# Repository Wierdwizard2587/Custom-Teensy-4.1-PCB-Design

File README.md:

# Custom Teensy 4.1 Microcontroller PCB

## Overview

This repository covers the design of my custom take on the Teensy 4.1 from PJRC. [Teensy 4.1 Site](https://www.pjrc.com/store/teensy41.html). I took inspiration from [jenschrs design](https://github.com/jenschr/Teensy-4.1-example) who incorporated usb-c rather than the intended USB-Micro, but lacked the SD slot, expandable RAM and flash memory, and PHY Ethernet IC and RJ45 Connection Like the original. 

This Design, following the Teensy 4.1 official Schematic Features a 6 layer design with dedicated GND and 3.3V plane’s, and possesses the same RAM, Flash, Boot loader and MCU components as the original Teensy 4.1, but the 3.3V regulator was swapped for a NCP692 regulator providing essentially the same specs. 

The Following are notable features in the Boards design:

- 2x USB-C connections, one for serial programming and power, and the other a host port for communication with serial to other devices
- Expandable IC footprints for a combination of either 2x additional 16mb PSRAM or 1x 16mb PSRAM and 1x 64mb FLASH
- DP83825L Ethernet PHY IC for interfacing with the MCU and the RJ45 Ethernet connector attached to the board for 10/100mbps internet
- micro SD slot

After assembling the first prototype with the supplied stencil from JLCPCB and a hot plate, and resolving a short issue from a solder bridge, The bootloader flashed the blink script to the memory and the board was able to achieve it, however serial communication wouldn’t work and windows device manager gave a error code 43. After a week of researching and forum questioning, I was able to locate the root problem to the ESD protection Diodes on the USB-C that I had used were rated for USB 2.0 and not 3.0, which was ruining the serial communication between my PC and the board. After desoldering these the board managed to show up on my PC and was finally able to communicate with it, albeit without ESD protection which can be replaced with a more suitable diode.

The Designing and assembly of this board taught me more design and assembly concepts such as:

- differential pairs and length matching design
- separation of analog and digital traces and components
- EMI ground shielding techniques
- positioning and selection of decoupling capacitors for electronic noise protection
- common via practices
- practice soldering SMD components with a hot plate and stencil effectively without overheating the temperature sensitive IC’s 
- more practical experience isolating faults in a circuit, such as isolating shorts, identifying faulty components
- examining signals with an oscilloscope to ensure Ethernet signal integrity.

all while managing to keep the design cost effective. This board is the most complex I have designed and successfully assembled to date and I am eager to take these skills learnt to the next level with the next project the future brings.

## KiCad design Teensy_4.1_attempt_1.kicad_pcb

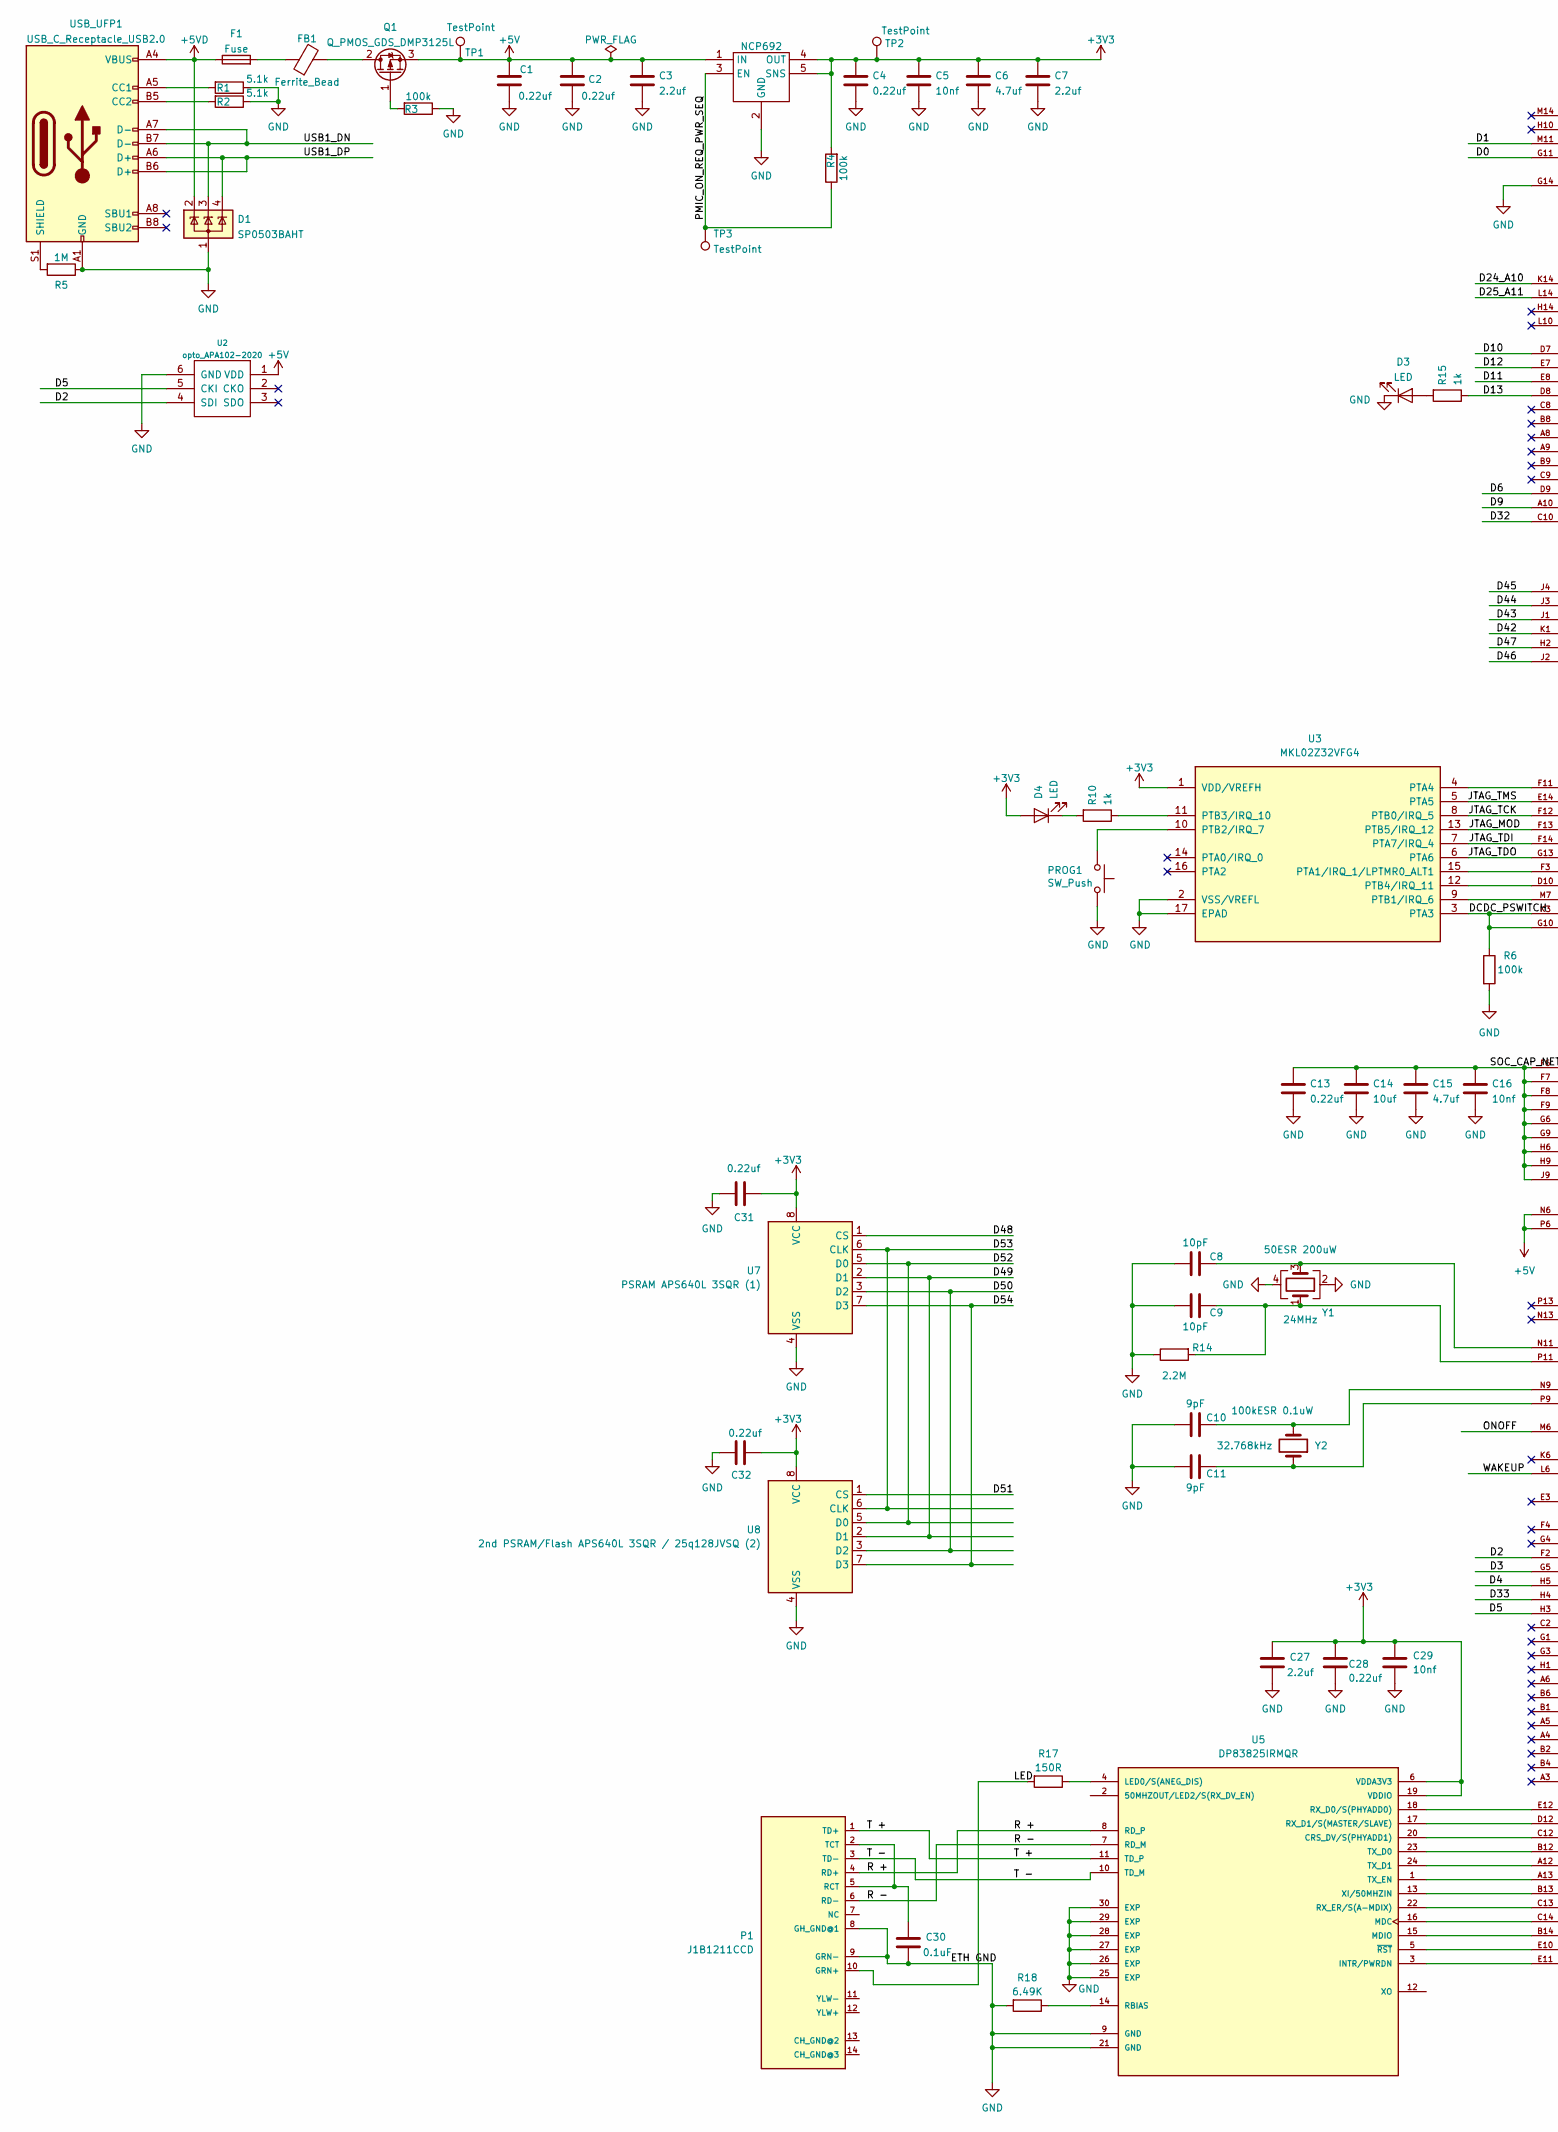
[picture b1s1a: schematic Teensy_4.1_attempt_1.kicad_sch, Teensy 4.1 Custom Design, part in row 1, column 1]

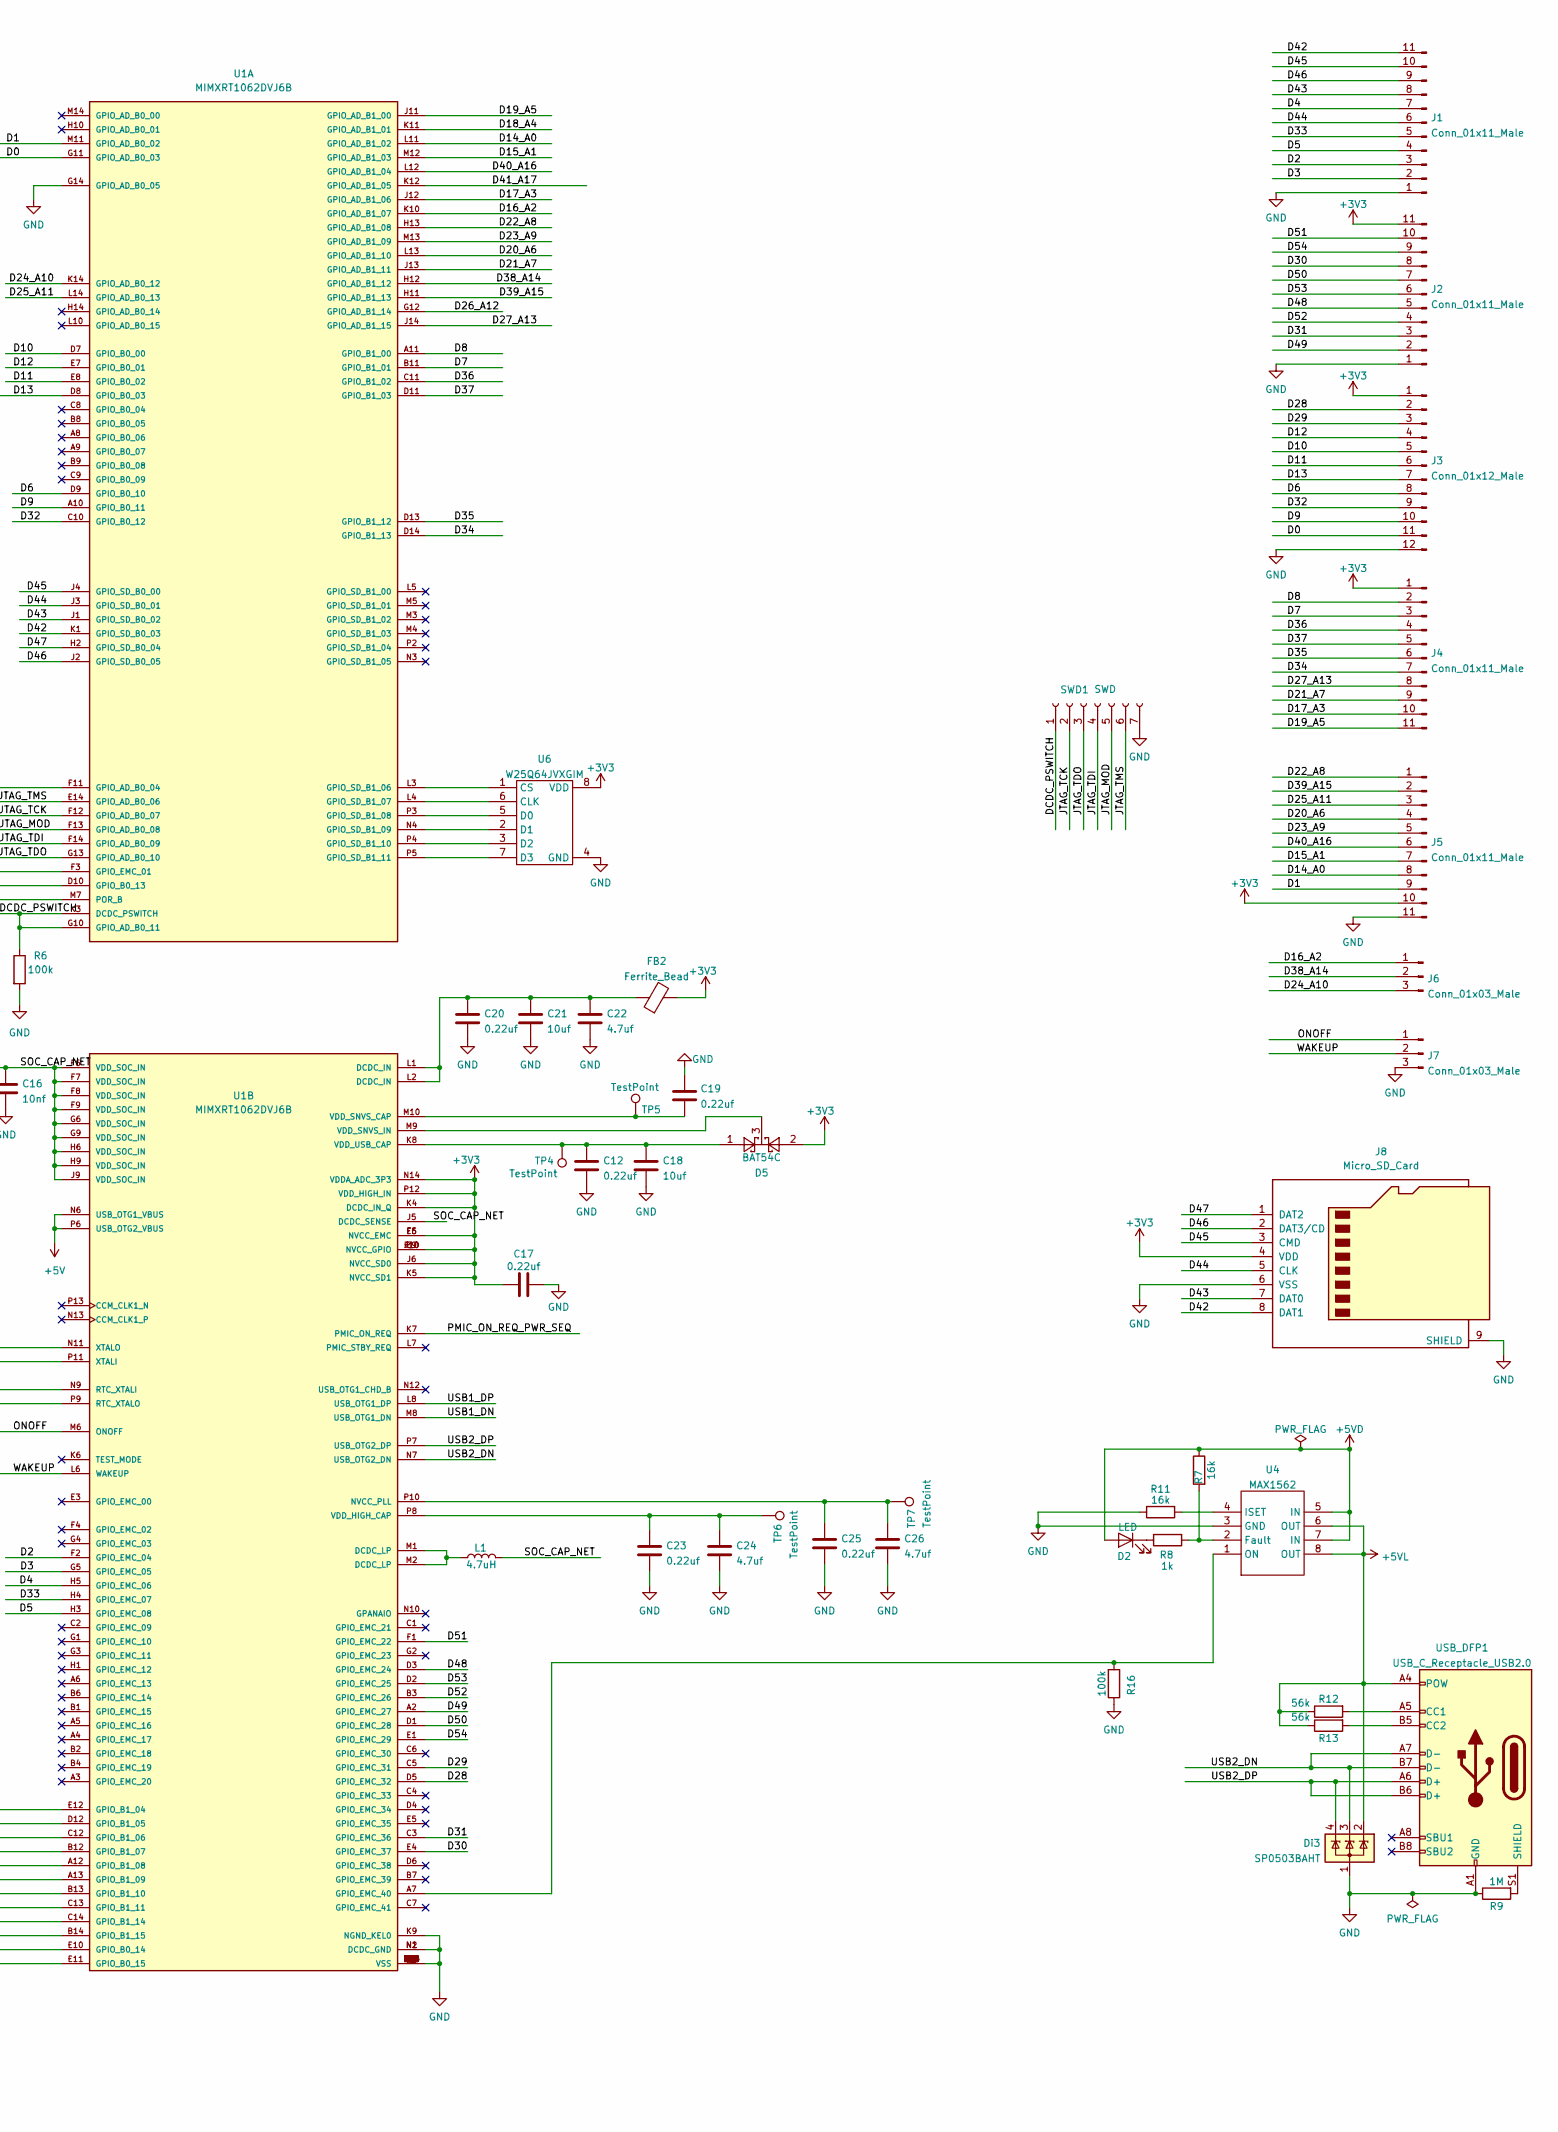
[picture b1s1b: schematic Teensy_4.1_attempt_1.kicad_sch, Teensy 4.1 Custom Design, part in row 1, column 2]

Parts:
C1, C2, C4, C12, C13, C17, C19, C20, C23, C25, C31, C32: 0.22uf; C_0603_1608Metric; MPN CC0603KRX7R6BB224
C3, C7: 2.2uf; C_0603_1608Metric; MPN CL10B225KP8NNNC
C5, C16: 10nf; C_0603_1608Metric; MPN 0603B103K160CT
C6, C15, C22, C24, C26: 4.7uf; C_0603_1608Metric; MPN CL10B475KQ8NQNC
C8, C9: 10pF; C_0603_1608Metric
C10, C11: 9pF; C_0603_1608Metric
C14, C18, C21: 10uf; C_0805_2012Metric; MPN GRM21BR71A106KA73K
C27: 2.2uf; C_0603_1608Metric; MPN CC0603KRX7R6BB224
C28: 0.22uf; C_0805_2012Metric; MPN GRM21BR71A106KA73K
C29: 10nf; C_0603_1608Metric; MPN CL10B475KQ8NQNC
C30: 0.1uF; C_0603_1608Metric; MPN CC0603KRX7R6BB224
D1: SP0503BAHT; SOT-143
D2, D3, D4: LED; LED_0603_1608Metric
D5: BAT54C; SOT-23
Di3: SP0503BAHT; SOT-143
F1: Fuse; R_0805_2012Metric; MPN 0ZCK0050FF2E
FB1, FB2: Ferrite_Bead; R_0805_2012Metric; MPN FBMH2012HM121-T‎
J1, J2, J4, J5: Conn_01x11_Male; PinHeader_1x11_P2.54mm_Vertical
J3: Conn_01x12_Male; PinHeader_1x12_P2.54mm_Vertical
J6, J7: Conn_01x03_Male; PinHeader_1x03_P2.54mm_Vertical
J8: Micro_SD_Card; microSD_HC_Hirose_DM3AT-SF-PEJM5
L1: 4.7uH; C_0805_2012Metric; MPN LQM21PN4R7MGRD
NCP692: OnSemi NCP692, fixed version; DFN-6-1EP_3x3mm_P0.95mm_EP1.7x2.6mm; MPN NCP692MN33T2G
P1: J1B1211CCD
PROG1: SW_Push; SW_Push_1P1T-SH_NO_CK_KMR2xxG; MPN KMR241GLFS
Q1: Q_PMOS_GDS_DMP3125L; SOT-23
R1, R2: 5.1k; R_0603_1608Metric; MPN RC0603FR-075K1L
R3, R4, R6, R16: 100k; R_0603_1608Metric
R5, R9: 1M; R_0603_1608Metric
R7, R11: 16k; R_0603_1608Metric
R8, R10, R15: 1k; R_0603_1608Metric
R12, R13: 56k; R_0603_1608Metric; MPN RMCF0603FT56K0
R14: 2.2M; R_0603_1608Metric
R17: 150R; R_0603_1608Metric
R18: 6.49K; R_0603_1608Metric
SWD1: SWD; PinHeader_1x07_P1.27mm_Vertical
TP1, TP2, TP3, TP4, TP5, TP6, TP7: TestPoint; TestPoint_Pad_D1.0mm
U1: MIMXRT1062DVJ6B; BGA196C80P14X14_1200X1200X152N; PARTREV 3
U2: opto_APA102-2020; LED-APA102-2020
U3: MKL02Z32VFG4; QFN-16-1EP_3x3mm_P0.5mm_EP1.9x1.9mm
U4: MAX1562; SO-8_3.9x4.9mm_P1.27mm
U5: DP83825IRMQR; XCVR_DP83825IRMQR; PARTREV A
U6: W25Q64JVXGIM; XSON8_4x4mm
U7: PSRAM APS640L 3SQR (1); SOP-8_3.9x4.9mm_P1.27mm
U8: 2nd PSRAM/Flash APS640L 3SQR / 25q128JVSQ (2); SOIC-8_5.3x5.3mm_P1.27mm
USB_DFP1: USB_C_Receptacle_USB2.0; USB_C_Receptacle_HRO_TYPE-C-31-M-12
USB_UFP1: USB_C_Receptacle_USB2.0; USB_C_Receptacle_HRO_TYPE-C-31-M-12
Y1: 24MHz; Crystal_SMD_2520-4Pin_2.5x2.0mm
Y2: 32.768kHz; Crystal_SMD_TXC_9HT11-2Pin_2.0x1.2mm_HandSoldering

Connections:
+3V3: C4.1, C5.1, C6.1, C7.1, C17.1, C27.1, C28.1, C29.1, C31.1, C32.1, D4.2 (A), D5.2, FB2.2, J2.11, J3.1, J4.1, J5.10, J8.4 (VDD), NCP692.4 (OUT), NCP692.5 (SNS), R4.2, TP2.1, U1.E6 (NVCC_EMC), U1.E9 (NVCC_GPIO), U1.F5 (NVCC_EMC), U1.F10 (NVCC_GPIO), U1.J6 (NVCC_SD0), U1.J10 (NVCC_GPIO), U1.K4 (DCDC_IN_Q), U1.K5 (NVCC_SD1), U1.N14 (VDDA_ADC_3P3), U1.P12 (VDD_HIGH_IN), U3.1 (VDD/VREFH), U5.6 (VDDA3V3), U5.19 (VDDIO), U6.8 (VDD), U7.8 (VCC), U8.8 (VCC)
+5V: C1.1, C2.1, C3.1, NCP692.1 (IN), NCP692.6 (IN), Q1.3 (S), TP1.1, U1.N6 (USB_OTG1_VBUS), U1.P6 (USB_OTG2_VBUS), U2.1 (VDD)
+5VD: D1.2 (K), D2.2 (A), F1.1, R7.1, U4.5 (IN), U4.7 (IN), USB_UFP1.A4 (VBUS), USB_UFP1.A9 (VBUS), USB_UFP1.B4 (VBUS), USB_UFP1.B9 (VBUS)
+5VL: Di3.2 (K), R12.1, R13.1, U4.6 (OUT), U4.8 (OUT), USB_DFP1.A4 (POW), USB_DFP1.A9 (POW), USB_DFP1.B4 (POW), USB_DFP1.B9 (POW)
/D0: J3.11, U1.G11 (GPIO_AD_B0_03)
/D1: J5.9, U1.M11 (GPIO_AD_B0_02)
/D2: J1.3, U1.F2 (GPIO_EMC_04), U2.4 (SDI)
/D3: J1.2, U1.G5 (GPIO_EMC_05)
/D4: J1.7, U1.H5 (GPIO_EMC_06)
/D5: J1.4, U1.H3 (GPIO_EMC_08), U2.5 (CKI)
/D6: J3.8, U1.D9 (GPIO_B0_10)
/D7: J4.3, U1.B11 (GPIO_B1_01)
/D8: J4.2, U1.A11 (GPIO_B1_00)
/D9: J3.10, U1.A10 (GPIO_B0_11)
/D10: J3.5, U1.D7 (GPIO_B0_00)
/D11: J3.6, U1.E8 (GPIO_B0_02)
/D12: J3.4, U1.E7 (GPIO_B0_01)
/D13: J3.7, R15.1, U1.D8 (GPIO_B0_03)
/D14_A0: J5.8, U1.L11 (GPIO_AD_B1_02)
/D15_A1: J5.7, U1.M12 (GPIO_AD_B1_03)
/D16_A2: J6.1, U1.K10 (GPIO_AD_B1_07)
/D17_A3: J4.10, U1.J12 (GPIO_AD_B1_06)
/D18_A4: U1.K11 (GPIO_AD_B1_01)
/D19_A5: J4.11, U1.J11 (GPIO_AD_B1_00)
/D20_A6: J5.4, U1.L13 (GPIO_AD_B1_10)
/D21_A7: J4.9, U1.J13 (GPIO_AD_B1_11)
/D22_A8: J5.1, U1.H13 (GPIO_AD_B1_08)
/D23_A9: J5.5, U1.M13 (GPIO_AD_B1_09)
/D24_A10: J6.3, U1.K14 (GPIO_AD_B0_12)
/D25_A11: J5.3, U1.L14 (GPIO_AD_B0_13)
/D26_A12: U1.G12 (GPIO_AD_B1_14)
/D27_A13: J4.8, U1.J14 (GPIO_AD_B1_15)
/D28: J3.2, U1.D5 (GPIO_EMC_32)
/D29: J3.3, U1.C5 (GPIO_EMC_31)
/D30: J2.8, U1.E4 (GPIO_EMC_37)
/D31: J2.3, U1.C3 (GPIO_EMC_36)
/D32: J3.9, U1.C10 (GPIO_B0_12)
/D33: J1.5, U1.H4 (GPIO_EMC_07)
/D34: J4.7, U1.D14 (GPIO_B1_13)
/D35: J4.6, U1.D13 (GPIO_B1_12)
/D36: J4.4, U1.C11 (GPIO_B1_02)
/D37: J4.5, U1.D11 (GPIO_B1_03)
/D38_A14: J6.2, U1.H12 (GPIO_AD_B1_12)
/D39_A15: J5.2, U1.H11 (GPIO_AD_B1_13)
/D40_A16: J5.6, U1.L12 (GPIO_AD_B1_04)
/D41_A17: U1.K12 (GPIO_AD_B1_05)
/D42: J1.11, J8.8 (DAT1), U1.K1 (GPIO_SD_B0_03)
/D43: J1.8, J8.7 (DAT0), U1.J1 (GPIO_SD_B0_02)
/D44: J1.6, J8.5 (CLK), U1.J3 (GPIO_SD_B0_01)
/D45: J1.10, J8.3 (CMD), U1.J4 (GPIO_SD_B0_00)
/D46: J1.9, J8.2 (DAT3/CD), U1.J2 (GPIO_SD_B0_05)
/D47: J8.1 (DAT2), U1.H2 (GPIO_SD_B0_04)
/D48: J2.5, U1.D3 (GPIO_EMC_24), U7.1 (CS)
/D49: J2.2, U1.A2 (GPIO_EMC_27), U7.2 (D1), U8.2 (D1)
/D50: J2.7, U1.D1 (GPIO_EMC_28), U7.3 (D2), U8.3 (D2)
/D51: J2.10, U1.F1 (GPIO_EMC_22), U8.1 (CS)
/D52: J2.4, U1.B3 (GPIO_EMC_26), U7.5 (D0), U8.5 (D0)
/D53: J2.6, U1.D2 (GPIO_EMC_25), U7.6 (CLK), U8.6 (CLK)
/D54: J2.9, U1.E1 (GPIO_EMC_29), U7.7 (D3), U8.7 (D3)
/DCDC_PSWITCH: R6.1, SWD1.1, U1.G10 (GPIO_AD_B0_11), U1.K3 (DCDC_PSWITCH), U3.3 (PTA3)
/JTAG_MOD: SWD1.5, U1.F13 (GPIO_AD_B0_08), U3.13 (PTB5/IRQ_12)
/JTAG_TCK: SWD1.2, U1.F12 (GPIO_AD_B0_07), U3.8 (PTB0/IRQ_5)
/JTAG_TDI: SWD1.4, U1.F14 (GPIO_AD_B0_09), U3.7 (PTA7/IRQ_4)
/JTAG_TDO: SWD1.3, U1.G13 (GPIO_AD_B0_10), U3.6 (PTA6)
/JTAG_TMS: SWD1.6, U1.E14 (GPIO_AD_B0_06), U3.5 (PTA5)
/LED: P1.10 (GRN+), R17.2
/ONOFF: J7.1, U1.M6 (ONOFF)
/PMIC_ON_REQ_PWR_SEQ: NCP692.3 (EN), R4.1, TP3.1, U1.K7 (PMIC_ON_REQ)
/R +: P1.4 (RD+), U5.8 (RD_P)
/R -: P1.6 (RD-), U5.7 (RD_M)
/SOC_CAP_NET: C13.1, C14.1, C15.1, C16.1, L1.2, U1.F6 (VDD_SOC_IN), U1.F7 (VDD_SOC_IN), U1.F8 (VDD_SOC_IN), U1.F9 (VDD_SOC_IN), U1.G6 (VDD_SOC_IN), U1.G9 (VDD_SOC_IN), U1.H6 (VDD_SOC_IN), U1.H9 (VDD_SOC_IN), U1.J5 (DCDC_SENSE), U1.J9 (VDD_SOC_IN)
/T +: P1.1 (TD+), U5.11 (TD_P)
/T -: P1.3 (TD-), U5.10 (TD_M)
/USB1_DN: D1.3 (K), U1.M8 (USB_OTG1_DN), USB_UFP1.A7 (D-), USB_UFP1.B7 (D-)
/USB1_DP: D1.4 (K), U1.L8 (USB_OTG1_DP), USB_UFP1.A6 (D+), USB_UFP1.B6 (D+)
/USB2_DN: Di3.3 (K), U1.N7 (USB_OTG2_DN), USB_DFP1.A7 (D-), USB_DFP1.B7 (D-)
/USB2_DP: Di3.4 (K), U1.P7 (USB_OTG2_DP), USB_DFP1.A6 (D+), USB_DFP1.B6 (D+)
/WAKEUP: J7.2, U1.L6 (WAKEUP)
GND: C1.2, C2.2, C3.2, C4.2, C5.2, C6.2, C7.2, C8.1, C9.1, C10.1, C11.1, C12.2, C13.2, C14.2, C15.2, C16.2, C17.2, C18.2, C19.1, C20.2, C21.2, C22.2, C23.2, C24.2, C25.2, C26.2, C27.2, C28.2, C29.2, C30.2, C31.2, C32.2, D1.1 (A), D3.1 (K), Di3.1 (A), J1.1, J2.1, J3.12, J5.11, J7.3, J8.6 (VSS), J8.9 (SHIELD), NCP692.2 (GND), NCP692.7 (GND), P1.8 (GH_GND@1), P1.9 (GRN-), PROG1.2, R1.1, R2.1, R3.1, R5.1, R6.2, R9.1, R11.1, R14.1, R16.1, R18.2, SWD1.7, U1.A1 (VSS), U1.A14 (VSS), U1.B5 (VSS), U1.B10 (VSS), U1.E2 (VSS), U1.E13 (VSS), U1.G7 (VSS), U1.G8 (VSS), U1.G14 (GPIO_AD_B0_05), U1.H7 (VSS), U1.H8 (VSS), U1.J7 (VSS), U1.J8 (VSS), U1.K2 (VSS), U1.K9 (NGND_KEL0), U1.K13 (VSS), U1.L9 (VSS), U1.N1 (DCDC_GND), U1.N2 (DCDC_GND), U1.N5 (VSS), U1.N8 (VSS), U1.P1 (VSS), U1.P14 (VSS), U2.6 (GND), U3.2 (VSS/VREFL), U3.17 (EPAD), U4.3 (GND), U5.9 (GND), U5.21 (GND), U5.25 (EXP), U5.26 (EXP), U5.27 (EXP), U5.28 (EXP), U5.29 (EXP), U5.30 (EXP), U6.4 (GND), U7.4 (VSS), U8.4 (VSS), USB_DFP1.A1 (GND), USB_DFP1.A12 (GND), USB_DFP1.B1 (GND), USB_DFP1.B12 (GND), USB_UFP1.A1 (GND), USB_UFP1.A12 (GND), USB_UFP1.B1 (GND), USB_UFP1.B12 (GND), Y1.2, Y1.4
unnamed: C20.1, C21.1, C22.1, FB2.1, U1.L1 (DCDC_IN), U1.L2 (DCDC_IN)
unnamed: D2.1 (K), R8.1
unnamed: D3.2 (A), R15.2
unnamed: D4.1 (K), R10.2
unnamed: F1.2, FB1.1
unnamed: L1.1, U1.M1 (DCDC_LP), U1.M2 (DCDC_LP)
unnamed: C30.1, P1.2 (TCT), P1.5 (RCT)
unnamed: FB1.2, Q1.2 (D)
unnamed: Q1.1 (G), R3.2
unnamed: U1.F11 (GPIO_AD_B0_04), U3.4 (PTA4)
unnamed: U1.D10 (GPIO_B0_13), U3.12 (PTB4/IRQ_11)
unnamed: U1.F3 (GPIO_EMC_01), U3.15 (PTA1/IRQ_1/LPTMR0_ALT1)
unnamed: U1.L3 (GPIO_SD_B1_06), U6.1 (CS)
unnamed: U1.L4 (GPIO_SD_B1_07), U6.6 (CLK)
unnamed: U1.P3 (GPIO_SD_B1_08), U6.5 (D0)
unnamed: U1.N4 (GPIO_SD_B1_09), U6.2 (D1)
unnamed: U1.P4 (GPIO_SD_B1_10), U6.3 (D2)
unnamed: U1.P5 (GPIO_SD_B1_11), U6.7 (D3)
unnamed: U1.M7 (POR_B), U3.9 (PTB1/IRQ_6)
unnamed: U1.E10 (GPIO_B0_14), U5.5 (~RST)
unnamed: U1.E11 (GPIO_B0_15), U5.3 (INTR/PWRDN)
unnamed: U1.E12 (GPIO_B1_04), U5.18 (RX_D0/S(PHYADD0))
unnamed: U1.D12 (GPIO_B1_05), U5.17 (RX_D1/S(MASTER/SLAVE))
unnamed: U1.C12 (GPIO_B1_06), U5.20 (CRS_DV/S(PHYADD1))
unnamed: U1.B12 (GPIO_B1_07), U5.23 (TX_D0)
unnamed: U1.A12 (GPIO_B1_08), U5.24 (TX_D1)
unnamed: U1.A13 (GPIO_B1_09), U5.1 (TX_EN)
unnamed: U1.B13 (GPIO_B1_10), U5.13 (XI/50MHZIN)
unnamed: U1.C13 (GPIO_B1_11), U5.22 (RX_ER/S(A-MDIX))
unnamed: U1.C14 (GPIO_B1_14), U5.16 (MDC)
unnamed: U1.B14 (GPIO_B1_15), U5.15 (MDIO)
unnamed: R16.2, U1.A7 (GPIO_EMC_40), U4.1 (ON)
unnamed: C25.1, C26.1, TP7.1, U1.P10 (NVCC_PLL)
unnamed: C10.2, U1.N9 (RTC_XTALI), Y2.2
unnamed: C11.2, U1.P9 (RTC_XTALO), Y2.1
unnamed: C23.1, C24.1, TP6.1, U1.P8 (VDD_HIGH_CAP)
unnamed: C19.2, TP5.1, U1.M10 (VDD_SNVS_CAP)
unnamed: D5.3, U1.M9 (VDD_SNVS_IN)
unnamed: C12.1, C18.1, D5.1, TP4.1, U1.K8 (VDD_USB_CAP)
unnamed: C9.2, R14.2, U1.P11 (XTALI), Y1.1
unnamed: C8.2, U1.N11 (XTALO), Y1.3
unnamed: PROG1.1, U3.10 (PTB2/IRQ_7)
unnamed: R10.1, U3.11 (PTB3/IRQ_10)
unnamed: R7.2, R8.2, U4.2 (Fault)
unnamed: R11.2, U4.4 (ISET)
unnamed: R17.1, U5.4 (LED0/S(ANEG_DIS))
unnamed: R18.1, U5.14 (RBIAS)
unnamed: R12.2, USB_DFP1.A5 (CC1)
unnamed: R13.2, USB_DFP1.B5 (CC2)
unnamed: R9.2, USB_DFP1.S1 (SHIELD)
unnamed: R1.2, USB_UFP1.A5 (CC1)
unnamed: R2.2, USB_UFP1.B5 (CC2)
unnamed: R5.2, USB_UFP1.S1 (SHIELD)

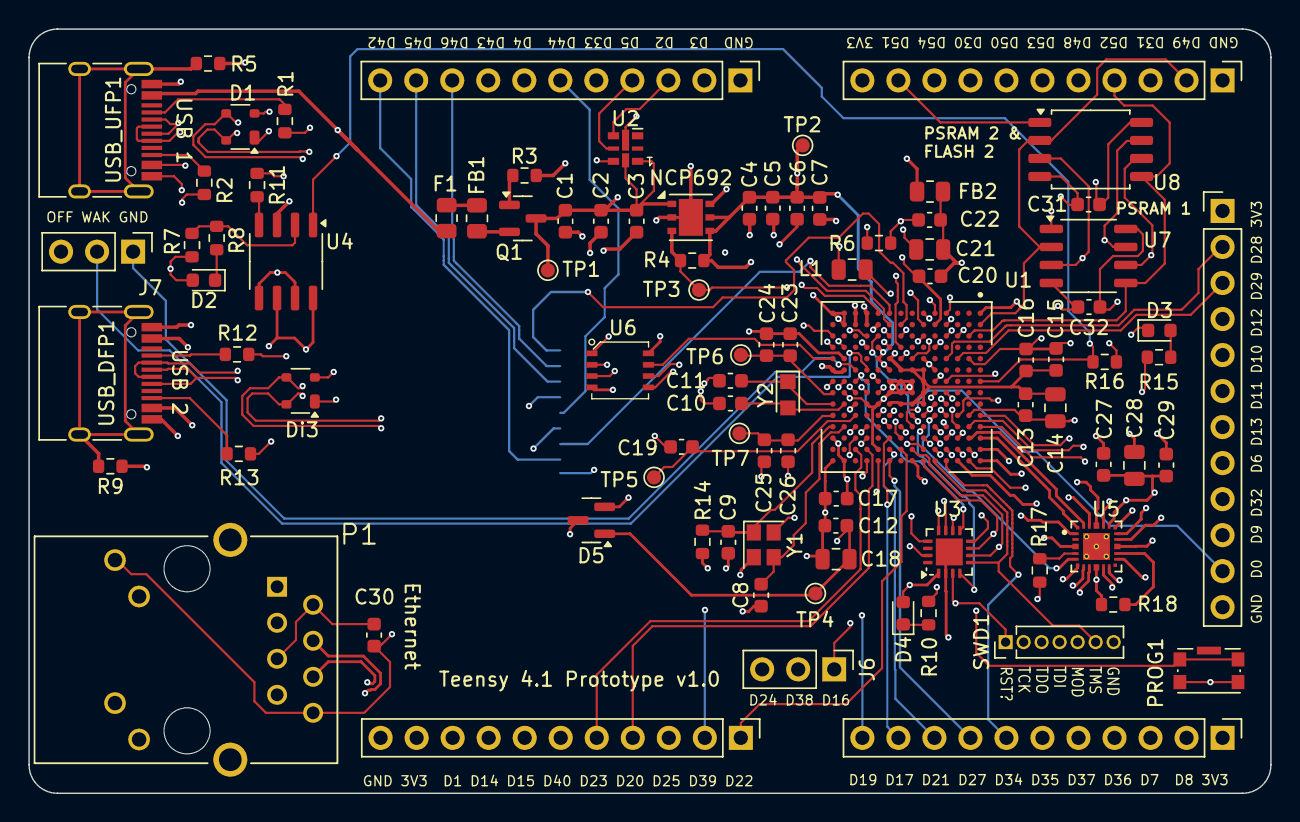
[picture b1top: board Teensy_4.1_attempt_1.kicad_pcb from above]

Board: 6 copper layers, 87.6 x 53.9 mm, 92 parts (1 on the bottom side), 129 nets.

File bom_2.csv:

Reference,Value,Footprint
C1,0.22uf,Capacitor_SMD:C_0603_1608Metric
C2,0.22uf,Capacitor_SMD:C_0603_1608Metric
C3,2.2uf,Capacitor_SMD:C_0603_1608Metric
C4,0.22uf,Capacitor_SMD:C_0603_1608Metric
C5,10nf,Capacitor_SMD:C_0603_1608Metric
C6,4.7uf,Capacitor_SMD:C_0603_1608Metric
C7,2.2uf,Capacitor_SMD:C_0603_1608Metric
C8,10pF,Capacitor_SMD:C_0603_1608Metric
C9,10pF,Capacitor_SMD:C_0603_1608Metric
C10,9pF,Capacitor_SMD:C_0603_1608Metric
C11,9pF,Capacitor_SMD:C_0603_1608Metric
C12,0.22uf,Capacitor_SMD:C_0603_1608Metric
C13,0.22uf,Capacitor_SMD:C_0603_1608Metric
C14,10uf,Capacitor_SMD:C_0805_2012Metric
C15,4.7uf,Capacitor_SMD:C_0603_1608Metric
C16,10nf,Capacitor_SMD:C_0603_1608Metric
C17,0.22uf,Capacitor_SMD:C_0603_1608Metric
C18,10uf,Capacitor_SMD:C_0805_2012Metric
C19,0.22uf,Capacitor_SMD:C_0603_1608Metric
C20,0.22uf,Capacitor_SMD:C_0603_1608Metric
C21,10uf,Capacitor_SMD:C_0805_2012Metric
C22,4.7uf,Capacitor_SMD:C_0603_1608Metric
C23,0.22uf,Capacitor_SMD:C_0603_1608Metric
C24,4.7uf,Capacitor_SMD:C_0603_1608Metric
C25,0.22uf,Capacitor_SMD:C_0603_1608Metric
C26,4.7uf,Capacitor_SMD:C_0603_1608Metric
C27,2.2uf,Capacitor_SMD:C_0603_1608Metric
C28,0.22uf,Capacitor_SMD:C_0805_2012Metric
C29,10nf,Capacitor_SMD:C_0603_1608Metric
C30,0.1uF,Capacitor_SMD:C_0603_1608Metric
C31,0.22uf,Capacitor_SMD:C_0603_1608Metric
C32,0.22uf,Capacitor_SMD:C_0603_1608Metric
D1,SP0503BAHT,Package_TO_SOT_SMD:SOT-143
D2,LED,LED_SMD:LED_0603_1608Metric
D3,LED,LED_SMD:LED_0603_1608Metric
D4,LED,LED_SMD:LED_0603_1608Metric
D5,BAT54C,Package_TO_SOT_SMD:SOT-23
Di3,SP0503BAHT,Package_TO_SOT_SMD:SOT-143
F1,Fuse,Resistor_SMD:R_0805_2012Metric
FB1,Ferrite_Bead,Resistor_SMD:R_0805_2012Metric
FB2,Ferrite_Bead,Resistor_SMD:R_0805_2012Metric
J1,Conn_01x11_Male,Connector_PinHeader_2.54mm:PinHeader_1x11_P2.54mm_Vertical
J2,Conn_01x11_Male,Connector_PinHeader_2.54mm:PinHeader_1x11_P2.54mm_Vertical
J3,Conn_01x12_Male,Connector_PinHeader_2.54mm:PinHeader_1x12_P2.54mm_Vertical
J4,Conn_01x11_Male,Connector_PinHeader_2.54mm:PinHeader_1x11_P2.54mm_Vertical
J5,Conn_01x11_Male,Connector_PinHeader_2.54mm:PinHeader_1x11_P2.54mm_Vertical
J6,Conn_01x03_Male,Connector_PinHeader_2.54mm:PinHeader_1x03_P2.54mm_Vertical
J7,Conn_01x03_Male,Connector_PinHeader_2.54mm:PinHeader_1x03_P2.54mm_Vertical
J8,Micro_SD_Card,Connector_Card:microSD_HC_Hirose_DM3AT-SF-PEJM5
L1,4.7uH,Capacitor_SMD:C_0805_2012Metric
NCP692,"OnSemi NCP692, fixed version",Package_DFN_QFN:DFN-6-1EP_3x3mm_P0.95mm_EP1.7x2.6mm
P1,J1B1211CCD,Teensy_Footprint_library:J1B1211CCD
PROG1,SW_Push,Button_Switch_SMD:SW_Push_1P1T-SH_NO_CK_KMR2xxG
Q1,Q_PMOS_GDS_DMP3125L,Package_TO_SOT_SMD:SOT-23
R1,5.1k,Resistor_SMD:R_0603_1608Metric
R2,5.1k,Resistor_SMD:R_0603_1608Metric
R3,100k,Resistor_SMD:R_0603_1608Metric
R4,100k,Resistor_SMD:R_0603_1608Metric
R5,1M,Resistor_SMD:R_0603_1608Metric
R6,100k,Resistor_SMD:R_0603_1608Metric
R7,16k,Resistor_SMD:R_0603_1608Metric
R8,1k,Resistor_SMD:R_0603_1608Metric
R9,1M,Resistor_SMD:R_0603_1608Metric
R10,1k,Resistor_SMD:R_0603_1608Metric
R11,16k,Resistor_SMD:R_0603_1608Metric
R12,56k,Resistor_SMD:R_0603_1608Metric
R13,56k,Resistor_SMD:R_0603_1608Metric
R14,2.2M,Resistor_SMD:R_0603_1608Metric
R15,1k,Resistor_SMD:R_0603_1608Metric
R16,100k,Resistor_SMD:R_0603_1608Metric
R17,150R,Resistor_SMD:R_0603_1608Metric
R18,6.49K,Resistor_SMD:R_0603_1608Metric
SWD1,SWD,Connector_PinHeader_1.27mm:PinHeader_1x07_P1.27mm_Vertical
TP1,TestPoint,TestPoint:TestPoint_Pad_D1.0mm
TP2,TestPoint,TestPoint:TestPoint_Pad_D1.0mm
TP3,TestPoint,TestPoint:TestPoint_Pad_D1.0mm
TP4,TestPoint,TestPoint:TestPoint_Pad_D1.0mm
TP5,TestPoint,TestPoint:TestPoint_Pad_D1.0mm
TP6,TestPoint,TestPoint:TestPoint_Pad_D1.0mm
TP7,TestPoint,TestPoint:TestPoint_Pad_D1.0mm
U1,MIMXRT1062DVJ6B,Teensy_Footprint_library:BGA196C80P14X14_1200X1200X152N
U2,opto_APA102-2020,LED_SMD:LED-APA102-2020
U3,MKL02Z32VFG4,Package_DFN_QFN:QFN-16-1EP_3x3mm_P0.5mm_EP1.9x1.9mm
U4,MAX1562,Package_SO:SO-8_3.9x4.9mm_P1.27mm
U5,DP83825IRMQR,Teensy_Footprint_library:XCVR_DP83825IRMQR
U6,W25Q64JVXGIM,Teensy_Footprint_library:XSON8_4x4mm
U7,PSRAM APS640L 3SQR (1),Package_SO:SOP-8_3.9x4.9mm_P1.27mm
U8,2nd PSRAM/Flash  APS640L 3SQR / 25q128JVSQ (2),Package_SO:SOIC-8_5.3x5.3mm_P1.27mm
USB_DFP1,USB_C_Receptacle_USB2.0,Connector_USB:USB_C_Receptacle_HRO_TYPE-C-31-M-12
USB_UFP1,USB_C_Receptacle_USB2.0,Connector_USB:USB_C_Receptacle_HRO_TYPE-C-31-M-12
Y1,24MHz,Crystal:Crystal_SMD_2520-4Pin_2.5x2.0mm
Y2,32.768kHz,Crystal:Crystal_SMD_TXC_9HT11-2Pin_2.0x1.2mm_HandSoldering

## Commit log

2025-05-08 commit BOM
2025-05-18 auto saves
2025-06-25 Organised Repo
2025-06-25 Update README.md
    Added images
2025-06-25 Update README.md
    added title
